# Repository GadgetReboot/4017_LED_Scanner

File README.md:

# 4017_LED_Scanner
8 LEDs scan back and forth like that futuristic black 80's Trans AM
<br><br>
<br><br><BR><BR>

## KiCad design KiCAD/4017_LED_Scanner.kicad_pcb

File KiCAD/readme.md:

KiCad schematic, PCB, and Gerbers

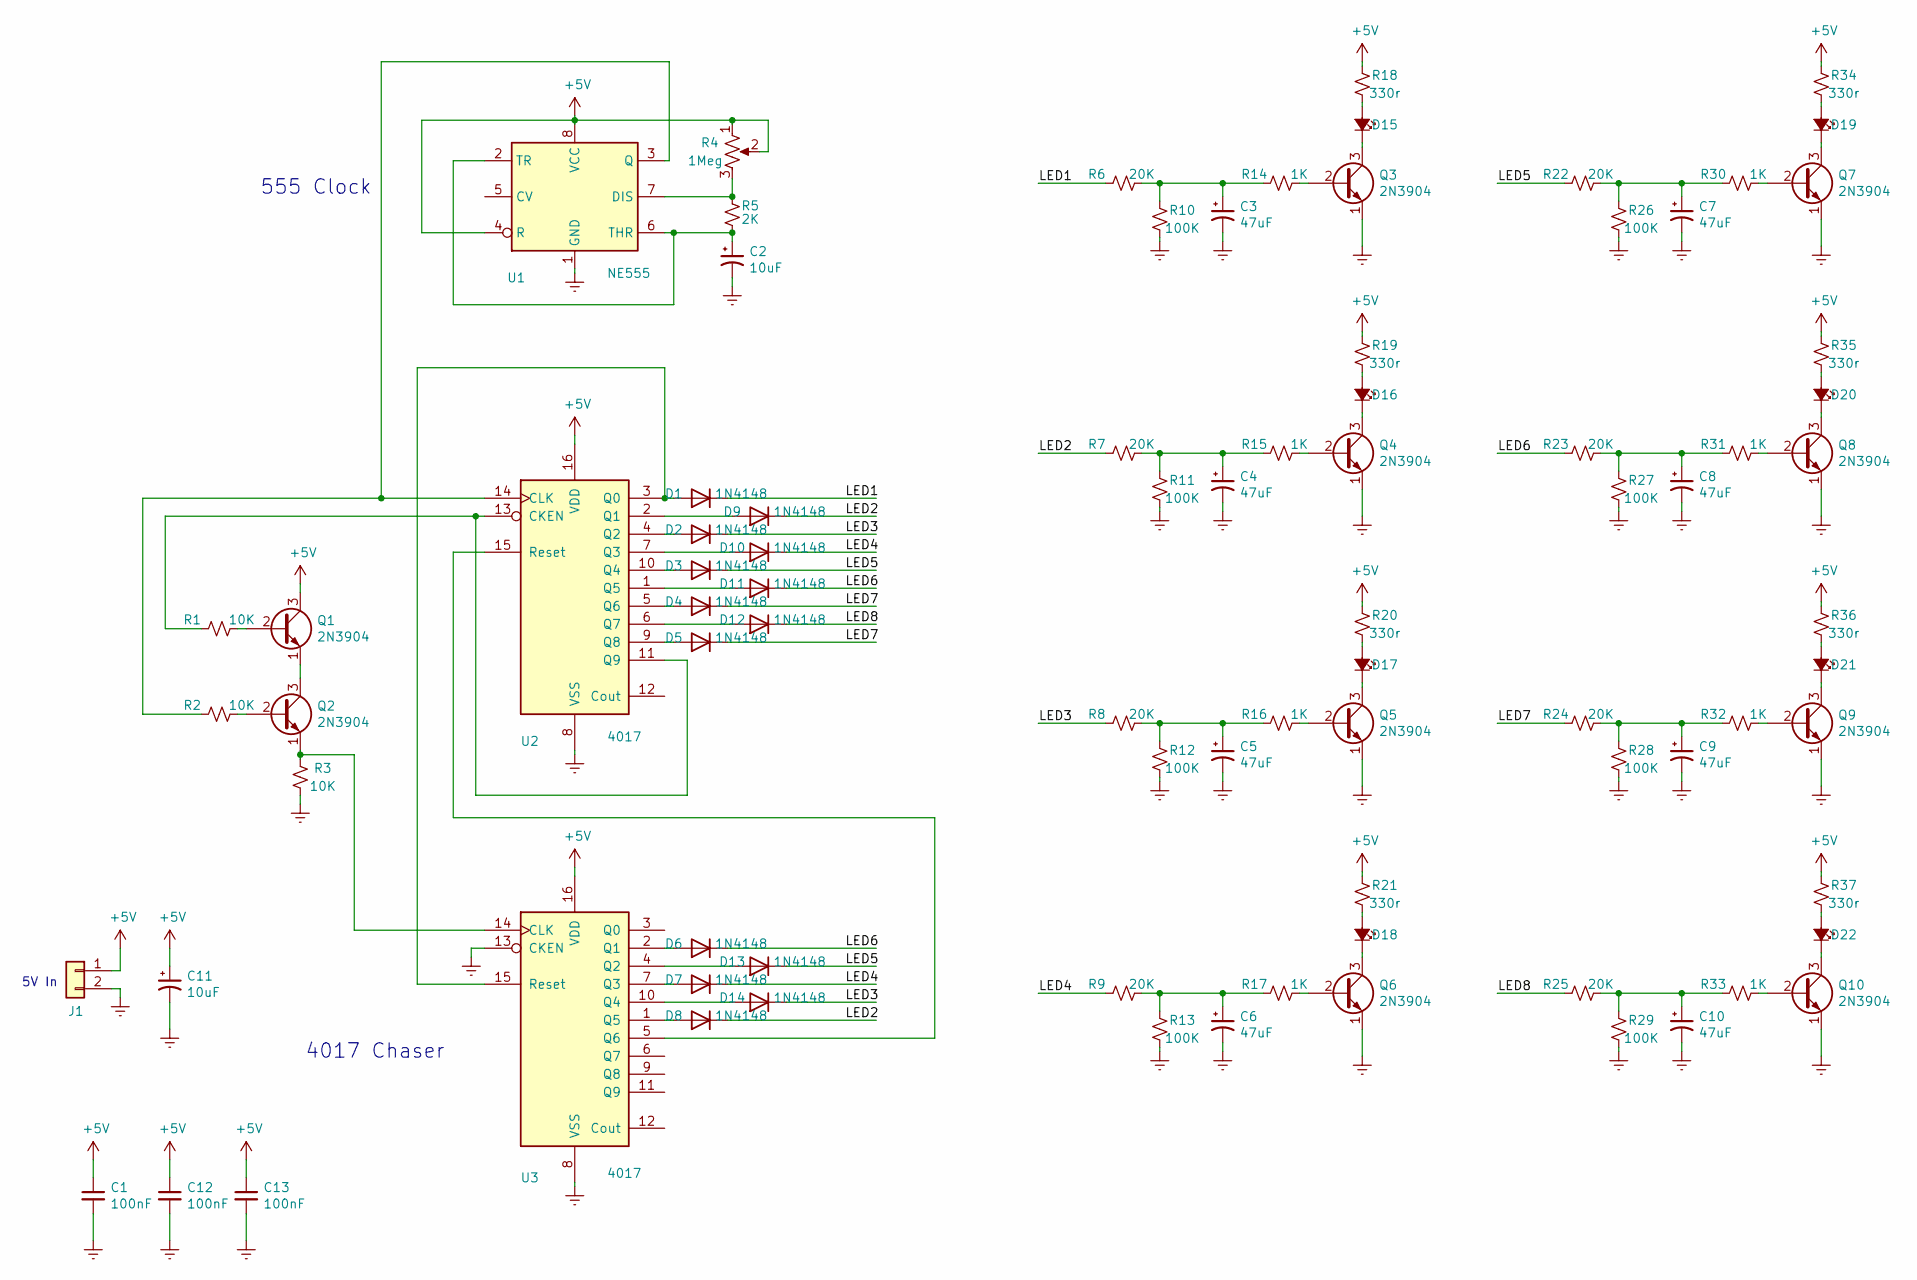
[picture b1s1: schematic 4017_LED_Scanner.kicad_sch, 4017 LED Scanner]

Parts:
C1, C12, C13: 100nF; C_Disc_D3.0mm_W1.6mm_P2.50mm
C2, C11: 10uF; CP_Radial_D5.0mm_P2.50mm
C3, C4, C5, C6, C7, C8, C9, C10: 47uF; CP_Radial_D5.0mm_P2.50mm
D1, D2, D3, D4, D5, D6, D7, D8, D9, D10, D11, D12, D13, D14: 1N4148; D_DO-35_SOD27_P3.81mm_Vertical_KathodeUp
D15, D16, D17, D18, D19, D20, D21, D22: LED_Small_ALT; LED_D5.0mm
J1: Conn_01x02; PinHeader_1x02_P2.54mm_Vertical
Q1, Q2, Q3, Q4, Q5, Q6, Q7, Q8, Q9, Q10: 2N3904; TO-92L_Inline
R1, R2, R3: 10K; R_Axial_DIN0207_L6.3mm_D2.5mm_P2.54mm_Vertical
R4: 1Meg; Potentiometer_ACP_CA9-H2,5_Horizontal
R5: 2K; R_Axial_DIN0207_L6.3mm_D2.5mm_P2.54mm_Vertical
R6, R7, R8, R9, R22, R23, R24, R25: 20K; R_Axial_DIN0207_L6.3mm_D2.5mm_P2.54mm_Vertical
R10, R11, R12, R13, R26, R27, R28, R29: 100K; R_Axial_DIN0207_L6.3mm_D2.5mm_P2.54mm_Vertical
R14, R15, R16, R17, R30, R31, R32, R33: 1K; R_Axial_DIN0207_L6.3mm_D2.5mm_P2.54mm_Vertical
R18, R19, R20, R21, R34, R35, R36, R37: 330r; R_Axial_DIN0207_L6.3mm_D2.5mm_P2.54mm_Vertical
U1: NE555; DIP-8_W7.62mm
U2, U3: 4017; DIP-16_W7.62mm

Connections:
+5V: C1.1, C11.1, C12.1, C13.1, J1.1, Q1.3 (C), R4.1, R4.2, R18.2, R19.2, R20.2, R21.2, R34.2, R35.2, R36.2, R37.2, U1.4 (R), U1.8 (VCC), U2.16 (VDD), U3.16 (VDD)
/LED1: D1.1 (K), R6.2
/LED2: D8.1 (K), D9.1 (K), R7.2
/LED3: D2.1 (K), D14.1 (K), R8.2
/LED4: D7.1 (K), D10.1 (K), R9.2
/LED5: D3.1 (K), D13.1 (K), R22.2
/LED6: D6.1 (K), D11.1 (K), R23.2
/LED7: D4.1 (K), D5.1 (K), R24.2
/LED8: D12.1 (K), R25.2
GNDREF: C1.2, C2.2, C3.2, C4.2, C5.2, C6.2, C7.2, C8.2, C9.2, C10.2, C11.2, C12.2, C13.2, J1.2, Q3.1 (E), Q4.1 (E), Q5.1 (E), Q6.1 (E), Q7.1 (E), Q8.1 (E), Q9.1 (E), Q10.1 (E), R3.1, R10.1, R11.1, R12.1, R13.1, R26.1, R27.1, R28.1, R29.1, U1.1 (GND), U2.8 (VSS), U3.8 (VSS), U3.13 (CKEN)
unnamed: C2.1, R5.2, U1.2 (TR), U1.6 (THR)
unnamed: C3.1, R6.1, R10.2, R14.2
unnamed: C4.1, R7.1, R11.2, R15.2
unnamed: C5.1, R8.1, R12.2, R16.2
unnamed: C6.1, R9.1, R13.2, R17.2
unnamed: C7.1, R22.1, R26.2, R30.2
unnamed: C8.1, R23.1, R27.2, R31.2
unnamed: C9.1, R24.1, R28.2, R32.2
unnamed: C10.1, R25.1, R29.2, R33.2
unnamed: D1.2 (A), U2.3 (Q0), U3.15 (Reset)
unnamed: D2.2 (A), U2.4 (Q2)
unnamed: D3.2 (A), U2.10 (Q4)
unnamed: D4.2 (A), U2.5 (Q6)
unnamed: D5.2 (A), U2.9 (Q8)
unnamed: D6.2 (A), U3.2 (Q1)
unnamed: D7.2 (A), U3.7 (Q3)
unnamed: D8.2 (A), U3.1 (Q5)
unnamed: D9.2 (A), U2.2 (Q1)
unnamed: D10.2 (A), U2.7 (Q3)
unnamed: D11.2 (A), U2.1 (Q5)
unnamed: D12.2 (A), U2.6 (Q7)
unnamed: D13.2 (A), U3.4 (Q2)
unnamed: D14.2 (A), U3.10 (Q4)
unnamed: D15.1 (K), Q3.3 (C)
unnamed: D15.2 (A), R18.1
unnamed: D16.1 (K), Q4.3 (C)
unnamed: D16.2 (A), R19.1
unnamed: D17.1 (K), Q5.3 (C)
unnamed: D17.2 (A), R20.1
unnamed: D18.1 (K), Q6.3 (C)
unnamed: D18.2 (A), R21.1
unnamed: D19.1 (K), Q7.3 (C)
unnamed: D19.2 (A), R34.1
unnamed: D20.1 (K), Q8.3 (C)
unnamed: D20.2 (A), R35.1
unnamed: D21.1 (K), Q9.3 (C)
unnamed: D21.2 (A), R36.1
unnamed: D22.1 (K), Q10.3 (C)
unnamed: D22.2 (A), R37.1
unnamed: Q1.1 (E), Q2.3 (C)
unnamed: Q1.2 (B), R1.1
unnamed: Q2.1 (E), R3.2, U3.14 (CLK)
unnamed: Q2.2 (B), R2.1
unnamed: Q3.2 (B), R14.1
unnamed: Q4.2 (B), R15.1
unnamed: Q5.2 (B), R16.1
unnamed: Q6.2 (B), R17.1
unnamed: Q7.2 (B), R30.1
unnamed: Q8.2 (B), R31.1
unnamed: Q9.2 (B), R32.1
unnamed: Q10.2 (B), R33.1
unnamed: R1.2, U2.11 (Q9), U2.13 (CKEN)
unnamed: R2.2, U1.3 (Q), U2.14 (CLK)
unnamed: R4.3, R5.1, U1.7 (DIS)
unnamed: U2.15 (Reset), U3.5 (Q6)

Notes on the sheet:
5V In
555 Clock
4017 Chaser

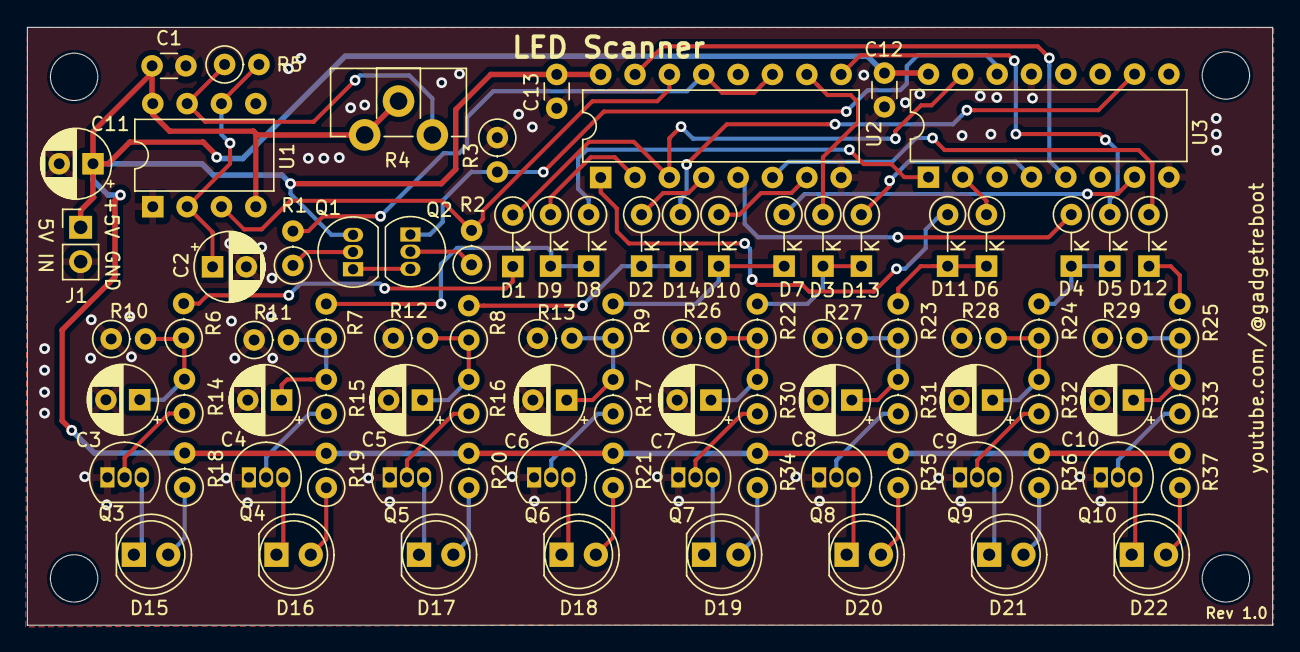
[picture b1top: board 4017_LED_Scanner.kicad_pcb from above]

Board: 2 copper layers, 92.1 x 44.2 mm, 86 parts (0 on the bottom side), 65 nets.
